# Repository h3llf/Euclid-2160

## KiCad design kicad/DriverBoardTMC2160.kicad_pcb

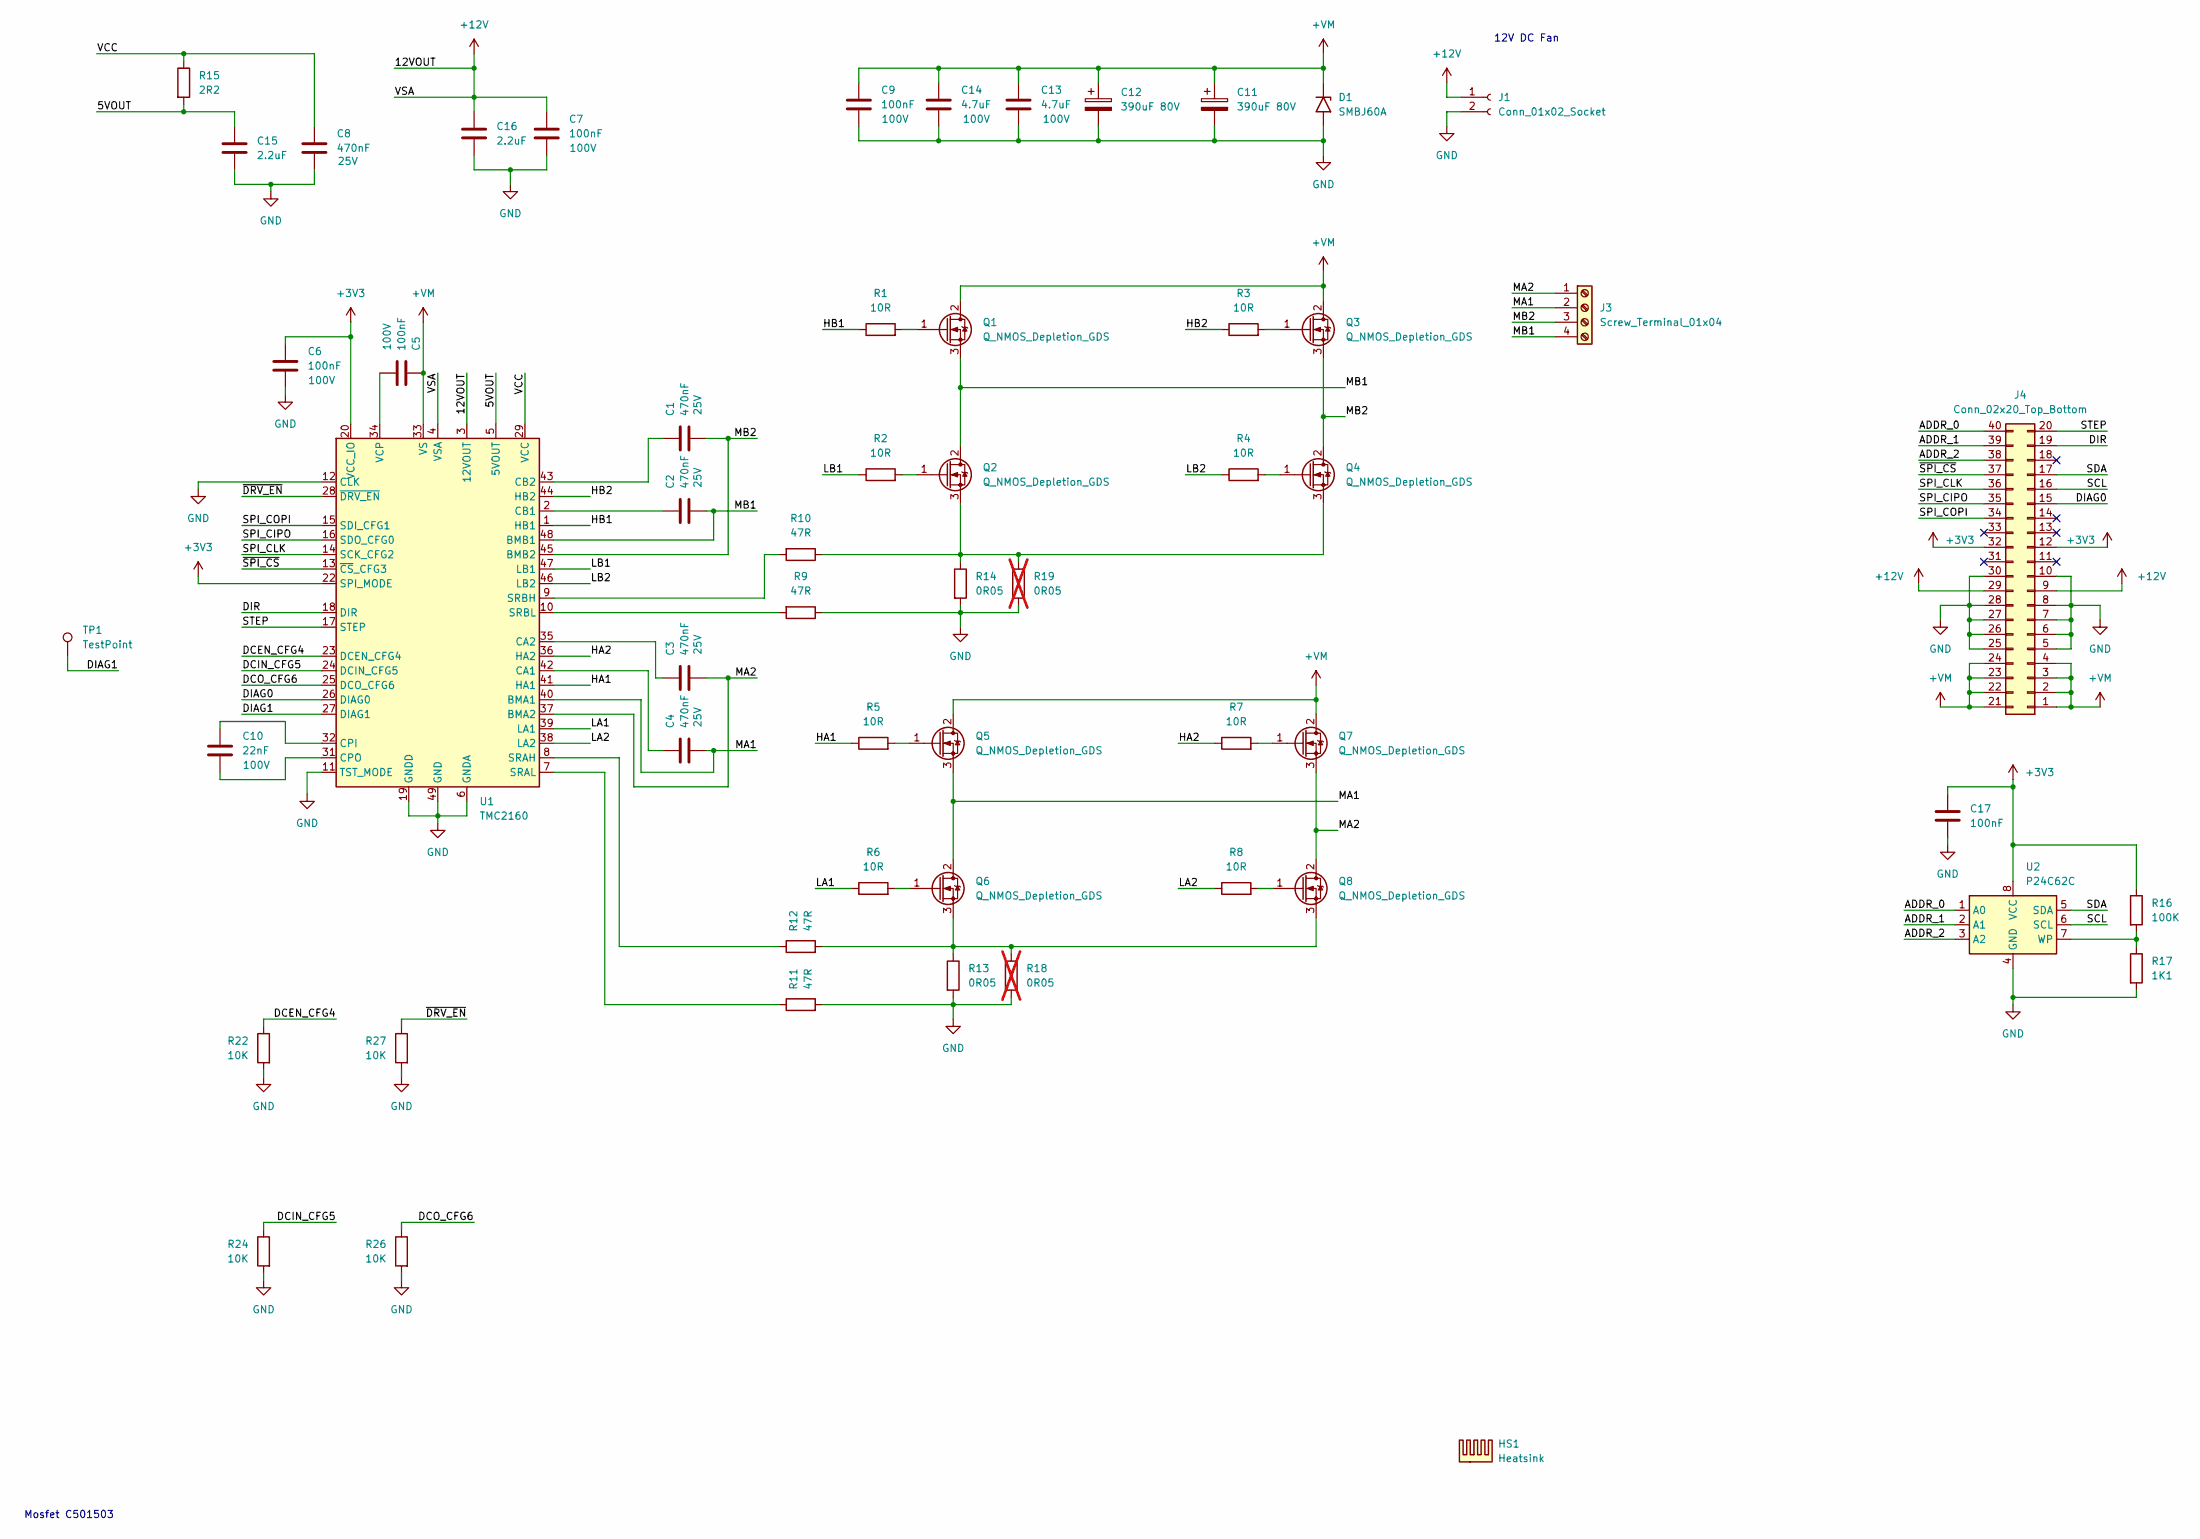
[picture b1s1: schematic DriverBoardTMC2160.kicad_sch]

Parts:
C1, C2, C3, C4, C8: 470nF; C_0603_1608Metric; Voltage 25V
C5, C6, C7, C9: 100nF; C_0603_1608Metric; Voltage 100V
C10: 22nF; C_0603_1608Metric; Voltage 100V
C11, C12: 390uF 80V; CP_Radial_D12.5mm_P5.00mm; LCSC C320012
C13, C14: 4.7uF; C_1210_3225Metric; Voltage 100V; LCSC C697607
C15, C16: 2.2uF; C_0603_1608Metric; LCSC C57895
C17: 100nF; C_0603_1608Metric
D1: SMBJ60A; D_SMB; LCSC C1974677
HS1: Heatsink; Heatsink_southbridge_35mm
J1: Conn_01x02_Socket; JST_XH_B2B-XH-A_1x02_P2.50mm_Vertical
J3: Screw_Terminal_01x04; TerminalBlock_Phoenix_MKDS-1,5-4_1x04_P5.00mm_Horizontal
J4: Conn_02x20_Top_Bottom; TX25-40P-LT-H1E
Q1, Q2, Q3, Q4, Q5, Q6, Q7, Q8: Q_NMOS_Depletion_GDS; PQFN-8-EP_6x5mm_P1.27mm_Generic; LCSC C431094
R1, R2, R3, R4, R5, R6, R7, R8: 10R; R_0603_1608Metric; LCSC C22859
R9, R10, R11, R12: 47R; R_0603_1608Metric
R13, R14: 0R05; R_2512_6332Metric; LCSC C2994645
R15: 2R2; R_0603_1608Metric; LCSC C112307
R16: 100K; R_0603_1608Metric
R17: 1K1; R_0603_1608Metric
R18, R19: 0R05; R_2512_6332Metric; LCSC C2994645; not fitted
R22, R24, R26, R27: 10K; R_0603_1608Metric; LCSC C22859
TP1: TestPoint; TestPoint_Pad_D2.0mm
U1: TMC2160; TQFP-48-1EP_7x7mm_P0.5mm_EP5x5mm_ThermalVias
U2: P24C62C; DFN-8-1EP_3x2mm_P0.5mm_EP1.36x1.46mm; LCSC C2977256

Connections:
+3V3: C6.1, C17.1, J4.12, J4.32, R16.1, U1.20 (VCC_IO), U1.21 (VCC_IO), U1.22 (SPI_MODE), U2.8 (VCC)
+12V: C7.1, C16.1, J1.1, J4.9, J4.29, U1.3 (12VOUT), U1.4 (VSA)
+VM: C5.1, C9.1, C11.1, C12.1, C13.1, C14.1, D1.1 (A1), J4.1, J4.2, J4.3, J4.4, J4.21, J4.22, J4.23, J4.24, Q1.2 (D), Q3.2 (D), Q5.2 (D), Q7.2 (D), U1.33 (VS)
/5VOUT: C15.1, R15.2, U1.5 (5VOUT)
/ADDR_0: J4.40, U2.1 (A0)
/ADDR_1: J4.39, U2.2 (A1)
/ADDR_2: J4.38, U2.3 (A2)
/DCEN_CFG4: R22.1, U1.23 (DCEN_CFG4)
/DCIN_CFG5: R24.1, U1.24 (DCIN_CFG5)
/DCO_CFG6: R26.1, U1.25 (DCO_CFG6)
/DIAG0: J4.15, U1.26 (DIAG0)
/DIAG1: TP1.1 (1_1), U1.27 (DIAG1)
/DIR: J4.19, U1.18 (DIR)
/HA1: R5.1, U1.41 (HA1)
/HA2: R7.1, U1.36 (HA2)
/HB1: R1.1, U1.1 (HB1)
/HB2: R3.1, U1.44 (HB2)
/LA1: R6.1, U1.39 (LA1)
/LA2: R8.1, U1.38 (LA2)
/LB1: R2.1, U1.47 (LB1)
/LB2: R4.1, U1.46 (LB2)
/MA1: C4.2, J3.2, Q5.3 (S), Q6.2 (D), U1.40 (BMA1)
/MA2: C3.2, J3.1, Q7.3 (S), Q8.2 (D), U1.37 (BMA2)
/MB1: C2.2, J3.4, Q1.3 (S), Q2.2 (D), U1.48 (BMB1)
/MB2: C1.2, J3.3, Q3.3 (S), Q4.2 (D), U1.45 (BMB2)
/SCL: J4.16, U2.6 (SCL)
/SDA: J4.17, U2.5 (SDA)
/SPI_CIPO: J4.35, U1.16 (SDO_CFG0)
/SPI_CLK: J4.36, U1.14 (SCK_CFG2)
/SPI_COPI: J4.34, U1.15 (SDI_CFG1)
/STEP: J4.20, U1.17 (STEP)
/VCC: C8.1, R15.1, U1.29 (VCC)
/~DRV_EN: R27.1, U1.28 (~DRV_EN)
/~SPI_CS: J4.37, U1.13 (~CS_CFG3)
GND: C6.2, C7.2, C8.2, C9.2, C11.2, C12.2, C13.2, C14.2, C15.2, C16.2, C17.2, D1.2 (A2), J1.2, J4.5, J4.6, J4.7, J4.8, J4.10, J4.25, J4.26, J4.27, J4.28, J4.30, R9.1, R11.2, R13.2, R14.2, R17.2, R18.2, R19.2, R22.2, R24.2, R26.2, R27.2, U1.6 (GNDA), U1.11 (TST_MODE), U1.12 (CLK), U1.19 (GNDD), U1.30 (GNDD), U1.49 (GND), U2.4 (GND), U2.9 (GND)
unnamed: Q1.1 (G), R1.2
unnamed: Q2.1 (G), R2.2
unnamed: Q2.3 (S), Q4.3 (S), R10.1, R14.1, R19.1
unnamed: Q3.1 (G), R3.2
unnamed: Q4.1 (G), R4.2
unnamed: Q5.1 (G), R5.2
unnamed: Q6.1 (G), R6.2
unnamed: Q6.3 (S), Q8.3 (S), R12.2, R13.1, R18.1
unnamed: Q7.1 (G), R7.2
unnamed: Q8.1 (G), R8.2
unnamed: C4.1, U1.42 (CA1)
unnamed: C3.1, U1.35 (CA2)
unnamed: C2.1, U1.2 (CB1)
unnamed: C1.1, U1.43 (CB2)
unnamed: C10.1, U1.32 (CPI)
unnamed: C10.2, U1.31 (CPO)
unnamed: R12.1, U1.8 (SRAH)
unnamed: R11.1, U1.7 (SRAL)
unnamed: R10.2, U1.9 (SRBH)
unnamed: R9.2, U1.10 (SRBL)
unnamed: C5.2, U1.34 (VCP)
unnamed: R16.2, R17.1, U2.7 (WP)

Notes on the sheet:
12V DC Fan
Mosfet C501503

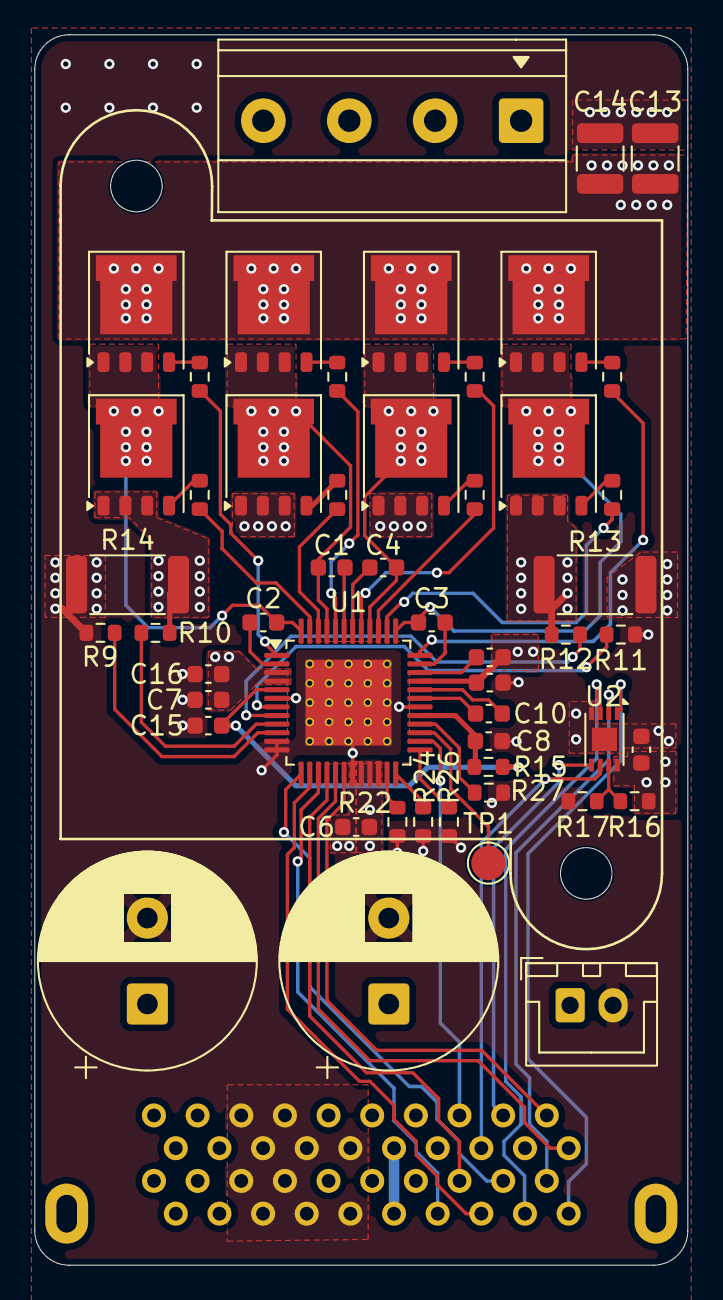
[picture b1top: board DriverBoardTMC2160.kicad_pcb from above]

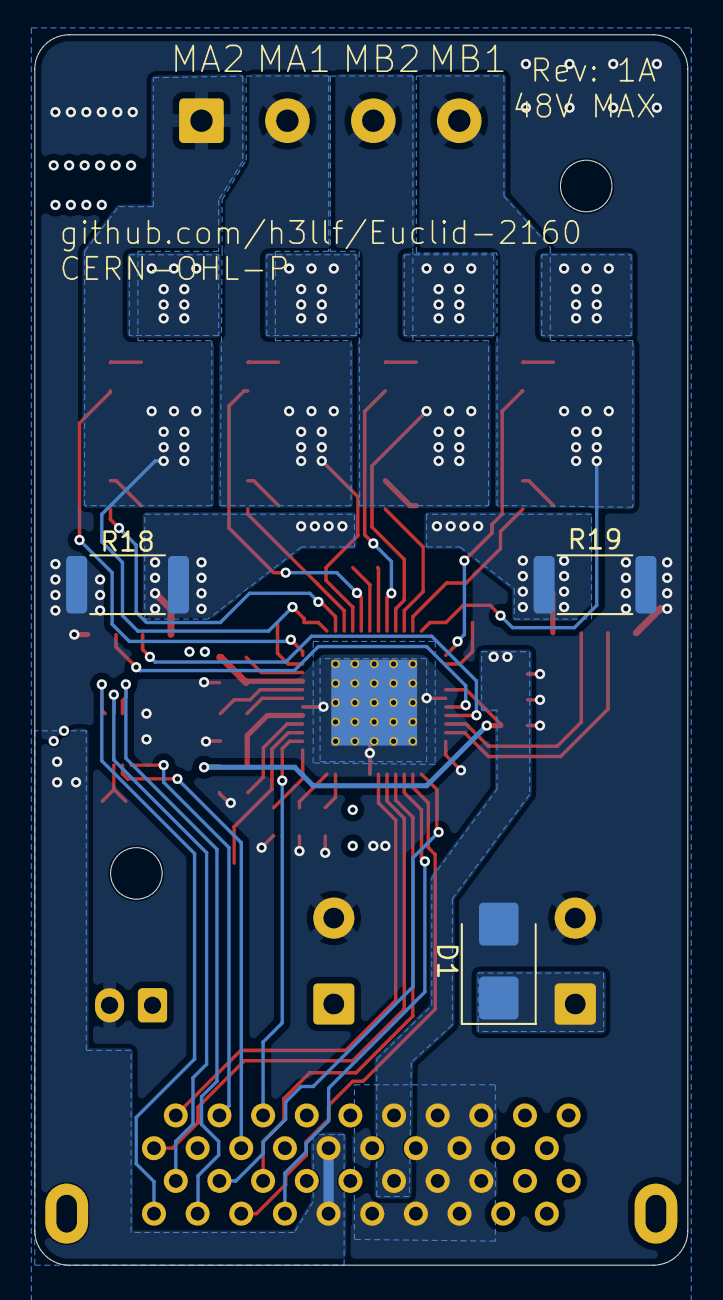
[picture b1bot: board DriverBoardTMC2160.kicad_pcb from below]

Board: 4 copper layers, 38.0 x 71.6 mm, 56 parts (3 on the bottom side), 57 nets.

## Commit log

2026-06-24 Initial
2026-06-25 Rev 1A
2026-06-25 Deleted old model

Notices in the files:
kicad/DriverBoardTMC2160.kicad_pcb:
CERN-OHL-P
